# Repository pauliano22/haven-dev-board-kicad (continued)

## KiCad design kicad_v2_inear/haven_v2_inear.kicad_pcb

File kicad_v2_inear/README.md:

# Haven v2 BTE in-ear unit: schematic

The small board in the in-ear unit: SPH0641 PDM mic (the primary mic; SELECT low = DMIC0) (bottom port, needs a hole through the
board), 100 nF decoupling, a 33 Ω series resistor on the mic's data line, six cable pads and two
speaker pads. Target outline about 6 × 6 mm, 2-layer, 0.6 mm.

The design notes, cable harness table and decisions are in `../kicad_v2_pod/README.md`. Both
schematics are generated by `tools/gen_v2_bte_schematic.py`.

For the 2-wire variant (pod mic only), leave the mic, C1 and R1 off, or skip this board and wire the speaker straight to cable W5/W6.

## Layout (`haven_v2_inear.kicad_pcb`)

Generated by `tools/gen_v2_inear_pcb.py`. The script places, routes, pours and fills, and writes the
design rules into the `.kicad_pro`. Results: DRC 0 violations, 0 unconnected, and schematic parity 0
(`kicad-cli pcb drc --schematic-parity --severity-all`).

- 6 × 6 mm, 2-layer, 0.6 mm, corner radius 0.8. The outline matches haven-hardware
  `mechanical_cad/v2_bte/board_inear_outline.dxf`. One board fits both ears.
- **Bottom (driver side):** U13 SPH0641LU4H-1. It is bottom-port (datasheet / DigiKey "Port
  Location: Bottom"), so its port sits on a plated 0.4 mm hole at the board centre. That hole is
  pad 3 (GND), added to the footprint and lined up with the shell's mic hole. The driver pads
  TP1/TP2 sit on the same face as the speaker.
- **Top (lateral side):** cable pads W1..W6, with C1 next to W1 and R1 in the DATA line. Nothing
  is placed within 1.4 mm of the port (`GASKET_KEEPOUT` rule area), so a 0.5 mm foam gasket can
  seal the board to the shell's mic hole.
- Rules (JLCPCB 2-layer standard): 0.15 mm tracks, 0.127 mm clearance, 0.3 / 0.55 mm vias,
  0.25 mm copper to edge. GND is poured on both layers.

Before ordering, check:
- The port hole and the paste on the four GND pads around it, against the Knowles land-pattern
  drawing. Solder must not flow into the port. If it might, trim the paste on the inner corners.
- The SPK and cable wire pads (0.8 mm) are for hand soldering 6-wire harness conductors under
  a microscope. Vias are in the pads, which is fine for hand soldering.

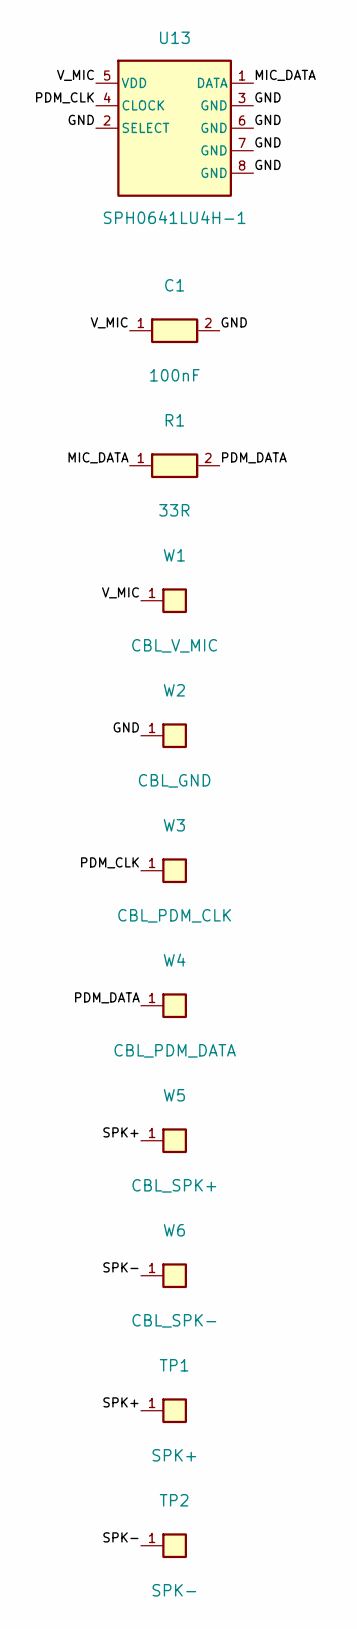
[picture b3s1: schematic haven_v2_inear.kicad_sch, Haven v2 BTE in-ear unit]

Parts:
C1: 100nF; C0201; MPN GRM033R60J104KE19D; LCSC C76928
R1: 33R; R0201; MPN ERJ1GNF33R0C; LCSC C717007
TP1: SPK+; Pad_1.2
TP2: SPK-; Pad_1.2
U13: SPH0641LU4H-1; MIC-SMD_5P_L3.5-W2.7-P0.82_SPH0641LU4H-1; MPN SPH0641LU4H-1; LCSC C2879853
W1: CBL_V_MIC; WirePad_0.8
W2: CBL_GND; WirePad_0.8
W3: CBL_PDM_CLK; WirePad_0.8
W4: CBL_PDM_DATA; WirePad_0.8
W5: CBL_SPK+; WirePad_0.8
W6: CBL_SPK-; WirePad_0.8

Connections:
/GND: C1.2, U13.2 (SELECT), U13.3 (GND), U13.6 (GND), U13.7 (GND), U13.8 (GND), W2.1
/MIC_DATA: R1.1, U13.1 (DATA)
/PDM_CLK: U13.4 (CLOCK), W3.1
/PDM_DATA: R1.2, W4.1
/SPK+: TP1.1, W5.1
/SPK-: TP2.1, W6.1
/V_MIC: C1.1, U13.5 (VDD), W1.1

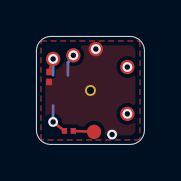
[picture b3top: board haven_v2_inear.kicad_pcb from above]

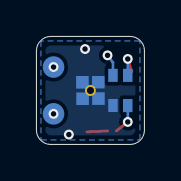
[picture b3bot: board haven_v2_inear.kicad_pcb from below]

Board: 2 copper layers, 6.0 x 6.0 mm, 11 parts (3 on the bottom side), 7 nets.

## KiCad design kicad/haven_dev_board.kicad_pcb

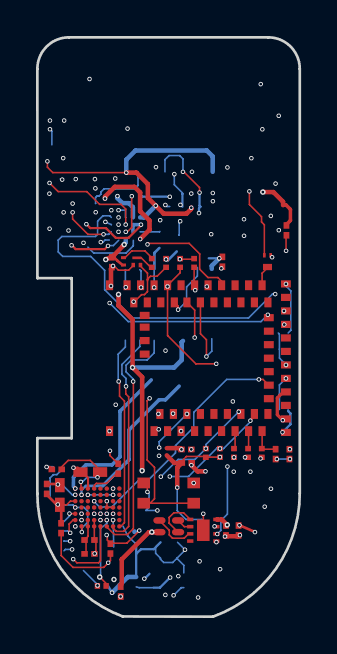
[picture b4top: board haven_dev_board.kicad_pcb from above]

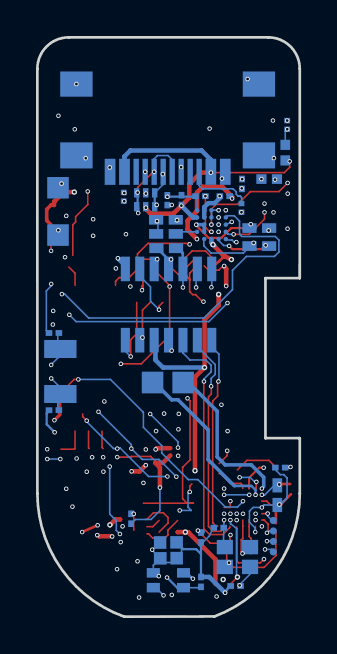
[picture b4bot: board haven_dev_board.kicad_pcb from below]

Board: 6 copper layers, 14.6 x 32.2 mm, 77 parts (39 on the bottom side), 61 nets.

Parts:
C1, C5, C7, C9, C10, C21, C29, C32, C36, C47: 1uF.1; C0201
C2, C14: 9pF.1; C0201
C3, C4: 4.7uF.1; C0201
C11, C12, C13, C27, C31, C38, C40, C42, C43, C44, C48: 100nF.1; C0201
C16, C20: 4.7uF, 10V.1; C0402
C17, C19, C22: 1uF >10V.1; C0201
C18: 10uF, >4V.1; C0402
C33, C34, C41: 10uF.1; C0402
C45, C46: GRM0335C1H330JA01D.1; b5c2858cad4e462ab76a8d0ccf4ade45
C49: C0402C103J3RACAUTO.1; cef4f92115b54348803d28f8706b0456
CRYSTAL1: CN4024M57620001.1; 6684822644394e4eba542a27714dd8a6
D2: PRTR5V0U2F.1; SON-6_L1.5-W1.0-P0.50-BL
J1: CLE-107-01-G-DV.1; CLE-107-01-X-DV
L2: 2.2uH.1; L0402
LED3: MHPA1010RGBDT.1; LED-ARRAY-SMD_4P-L1.0-W1.0-TR-RD
MDBT531: MDBT53.1; MDBT53
Q1: CSD23382F4.1; PICOSTAR-3_L1.0-W0.6-P0.35-TL
Q2: CSD13380F3T.1; PICOSTAR-3_L0.7-W0.6-P0.40-TL
R2, R3: 10kΩ.1; R0201
R4: 510Ω.1; R0201
R5, R9: 2kΩ.1; R0201
R6: 51kΩ.1; R0201
R7, R8: 5.1kΩ.1; R0201
R13: 37.4kΩ, 1%.1; R0402
R21: 0R; R0402
R23, R26: 27Ω.1; R0201
R27: 2.2Ω.1; R0201
R28: RC0201FR-07220RL.1; ea94e26560f84db4a6862024f5c3efa7
SW1: TS2819A 230GF.1; SW-SMD_4P-L2.8-W1.9-P1.16-LS3.0
TP_BAT+: pad; free_pad
TP_BAT-: pad; free_pad
TP_BCLK: pad; free_pad
TP_DIN: pad; free_pad
TP_DOUT: pad; free_pad
TP_LRCLK: pad; free_pad
TP_SPK+: pad; free_pad
TP_SPK-: pad; free_pad
U2: BQ25120AYFPR.1; DSBGA-25_L2.5-W2.6-R5-C5-P0.40-BL
U3: AP22916BCA4-7.1; X1-WLB0808-4_L0.8-W0.8-P0.40-TL
U4: XL-0201SURC.1; LED-SMD_L0.65-W0.35-P0.41_XL-0201SURC
U5: KTD2026.1; DFN-8_L1.5-W1.5-P0.40-BL-EP
U8: 1MΩ.1; R0201
U12: GT-USB-9047A.1; USB-C-SMD_GT-USB-9047A
U13: SPH0641LU4H-1.1; MIC-SMD_5P_L3.5-W2.7-P0.82_SPH0641LU4H-1
U15: ADAU1860BCBZRL.1; BGA-56_L3.0-W2.7-P0.35-R8-C7-TL
X1: Q13FC1350000200.1; FC-135R_L3.2-W1.5

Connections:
3V3: C5.2, C17.1, C29.2, C48.1, J1.10, LED3.1, U2.C5, U4.1, U5.5
#ERROR: MDBT531.3, Q2.1, U8.1
$1N48: R7.2, U12.A5
$1N49: R8.2, U12.B5
$1N65: C10.1, U2.C4
$1N98: C3.1, MDBT531.44, R27.2
$1N117: Q2.3, R4.2
$1N119: R4.1, U4.2
$1N151: C31.1, C36.1, U15.A3, U15.B3
$1N2586: C32.1, U15.G4
$1N16368: C45.1, CRYSTAL1.3, R28.1
+1.8V: C1.2, C4.2, C18.1, C20.2, J1.9, L2.2, MDBT531.38, MDBT531.41, Q1.2, R2.1, R3.1, U2.B5, U3.A2
BCLK: MDBT531.59, TP_BCLK.1, U15.B2
CC_#CD: MDBT531.26, U2.E2
CC_#PG: MDBT531.16, U2.D4
DAC_ENABLE: MDBT531.37, U15.E4
DAC_N: TP_SPK-.1, U15.G1
DAC_P: TP_SPK+.1, U15.F2
DIN: MDBT531.60, TP_DIN.1, U15.C1
DOUT: MDBT531.56, TP_DOUT.1, U15.B1
GND: C1.1, C2.1, C3.2, C4.1, C5.1, C7.2, C9.2, C10.2, C11.1, C12.1, C13.2, C14.1, C16.1, C17.2, C18.2, C19.2, C20.1, C21.1, C22.2, C27.1, C29.1, C31.2, C32.2, C33.1, C34.2, C36.2, C38.1, C40.2, C41.2, C42.1, C43.2, C44.2, C45.2, C46.1, C47.2, C48.2, C49.1, CRYSTAL1.2, CRYSTAL1.4, D2.2, J1.7, MDBT531.1, MDBT531.24, MDBT531.42, MDBT531.61, Q2.2, R6.1, R7.1, R8.1, SW1.3, SW1.4, TP_BAT-.1, U2.A1, U2.A5, U2.C1, U2.C2, U2.D1, U2.D5, U3.B1, U5.8, U5.9, U8.2, U12.12, U12.13, U12.14, U12.15, U12.A1B12, U12.A12B1, U13.2, U13.3, U13.6, U13.7, U13.8, U15.A1, U15.A4, U15.B4, U15.D6, U15.D7, U15.E6, U15.F1, U15.G3, U15.G7
INT: MDBT531.14, U2.D2
IO1: J1.11, MDBT531.9
IO2: J1.12, MDBT531.11
IO3: J1.14, MDBT531.13
LRCLK: MDBT531.57, TP_LRCLK.1, U15.C2
LSCTRL: MDBT531.27, U2.E3
MR#: Q1.1, SW1.1, SW1.2, U2.E1
ON+BTN: MDBT531.22, Q1.3
PDMCLK: U13.4, U15.C4
PDMDIN: U13.1, U15.C5
RESETN: C49.2, J1.5, MDBT531.6, U2.D3
RGB_B: LED3.4, U5.2
RGB_G: LED3.3, U5.3
RGB_R: LED3.2, U5.4
SCL: MDBT531.8, R3.2, U2.E5, U5.6
SCL1: MDBT531.45, R9.2, U15.C7
SDA: MDBT531.12, R2.2, U2.E4, U5.7
SDA1: MDBT531.47, R5.2, U15.C6
SENSORS_ENABLE: MDBT531.55, U3.B2
SW: L2.1, U2.A4
SWCLK: J1.1, MDBT531.2
SWDIO: J1.3, MDBT531.4
TCK: J1.8, U15.A5
TDI: J1.2, U15.A8
TDO: J1.4, U15.A7
TMS: J1.6, U15.A6
TS: R6.2, R13.1, U2.C3
USB_D+: MDBT531.46, R23.2
USB_D-: MDBT531.48, R26.2
USB_DM: D2.1, D2.6, R26.1, U12.A7, U12.B7
USB_DP: D2.3, D2.4, R23.1, U12.A6, U12.B6
VCC: C19.1, R21.2, U2.B1, U2.B2
VUSB: C22.1, D2.5, R13.2, R27.1, U2.A2, U12.A4B9, U12.A9B4
V_BAT: C21.2, R21.1, TP_BAT+.1
V_LS: C7.1, C11.2, C12.2, C13.1, C27.2, C33.2, C34.1, C38.2, C40.1, C41.1, C42.2, C43.1, C44.1, C47.1, J1.13, R5.1, R9.1, U3.A1, U13.5, U15.A2, U15.B5, U15.D1, U15.E1, U15.F3, U15.F7, U15.G2
V_PMID: C9.1, C16.2, U2.A3, U2.B3, U2.B4
XL1: C14.2, MDBT531.34, X1.1
XL2: C2.2, MDBT531.36, X1.2
XTALI: C46.2, CRYSTAL1.1, U15.B7
XTALO: R28.2, U15.B6

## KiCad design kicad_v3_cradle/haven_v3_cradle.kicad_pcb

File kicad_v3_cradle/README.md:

# Haven v3 charging cradle (2026-11-14)

A desk cradle that charges both v3 pods from any USB-C charger. No battery, no charging chip: each pod has its own
(nPM1100). The cradle only brings 5 V to the pods' two spring pins.

**Why a cradle and not a charging case:** a case carries its own battery and charger board and is a project of its
own. The first pair only needs to charge; this does that with four cheap parts. A case can come later.

## Parts

| Part | Made by | Source |
|---|---|---|
| Dock board, 41 x 51.5 mm, 2 layers, 1.6 mm, ENIG (the pads must be gold) | JLCPCB, fully assembled, nothing to solder | `tools/gen_cradle_v3_pcb.py` -> `haven_v3_cradle.kicad_pcb`, fab files in `fab/v3_cradle/` |
| Base, frame, lid (printed, about 9 g each) | any resin or FDM print service | `hardware/mechanical_cad/v3_slim/cradle_v3.py` -> `cradle_v3_{base,frame,lid}.stl` |
| 8 disc magnets 5 x 2 mm N52, 4 screws M2 x 8 self-tapping | bought | glued into the frame top and lid underside; screws go through frame and board into the base |

Board parts (LCSC numbers from memory, **check them at the JLCPCB quote**): J1 USB-C TYPE-C-31-M-12 (C165948),
R1 / R2 5.1 kohm 0603 (C23186, tell the charger to give 5 V), C1 10 uF 0603 (C19702). Four bare pads CP1-CP4.

## How a pod sits

- Head-side face down in a pocket shaped like the pod. Its two spring pins (pod board P1 = VBUS, P2 = GND) land on two
  1.8 mm gold pads on a tongue of the board; "+" and "-" are printed beside them.
- The pod shell now has a **flat contact land** around the pins (z = -4.4, 5.4 x 4.0 mm, wall thickened inside to
  0.8 mm; `LAND_*` in `pod_v3_styled.py`). Before this the face sloped about 25 degrees there and a flat pad would
  have hit the shell first. With the 4.5 mm pin the tip stands 0.5 mm proud of the land and the pad pushes it in 0.5 mm
  (half its 1.0 mm working travel).
- The rest of the pod's curved head side goes through a hole in the board into a printed cup with 0.3 mm clearance, so
  the pod rests on the land, not the cup.
- The lid rests on the pods (0.3 mm above the frame) and four magnet pairs pull it down, so the magnets' pull presses
  the pods onto the pads. Spring-pin force: 130 gf +-20 % each at the 1.0 mm working point (datasheet); at 0.5 mm it
  is less, not given.
- The speaker cable leaves through an open slot at each pocket's cable end; the lid has a groove over it.
- Both pods are the same part (the v3 pod is mirror-symmetric across its width, so the same pod rotated serves the
  other ear), so both pockets are the same.

## Checks run

- Board: KiCad DRC 0 errors, 0 unconnected, 2 silkscreen warnings. Board outline, holes, tongues, pads and screws are
  read from `cradle_v3_layout.json`, written by the cradle script, so the two cannot drift apart.
- Cradle script asserts: the pod never dips into the board outside the holes; every pad is on board; base, frame and
  lid do not overlap; the lid reaches the pods. Section picture: `cradle_v3_section.png`.

Review (2026-11-14, after the first build):
- Polarity traced from the pod board file to the dock board file: on both pods P1 (VBUS) lands on a VBUS pad and P2
  (GND) on a GND pad. A pod put in turned around lands its pins on the printed cup: no contact, so it cannot be
  reverse-powered. Upside down, the pins face up: no contact.
- The real shell meshes placed in the cradle: no overlap with the base or frame (closest 0.05 mm to the cups, 0.15 mm
  to the pocket walls); the lid presses 0.06 mm into the pod lids, which is the intended contact.
- Added after review: a thumb notch in the frame at the cable end, so the magnet lid can be lifted.
- Screws: M2 x 8 goes through 4.2 mm of frame and the 1.6 mm board and 2.2 mm into the 3 mm base; it does not come
  out the bottom.

## Not checked / open

- Nothing printed or built. Magnet strength in practice; real contact force at 0.5 mm; print tolerances.
- No fuse and no ESD part: a coin across a + and - pad shorts the charger's 5 V (USB chargers current-limit; cheap ones
  may not). The pads are under the pods, recessed in the pockets.
- No parking spot for the in-ear pieces; they hang out on their cables.
- Only the A4/B9 VBUS pins of the socket are wired (all four VBUS contacts are one wire inside a USB-C plug).

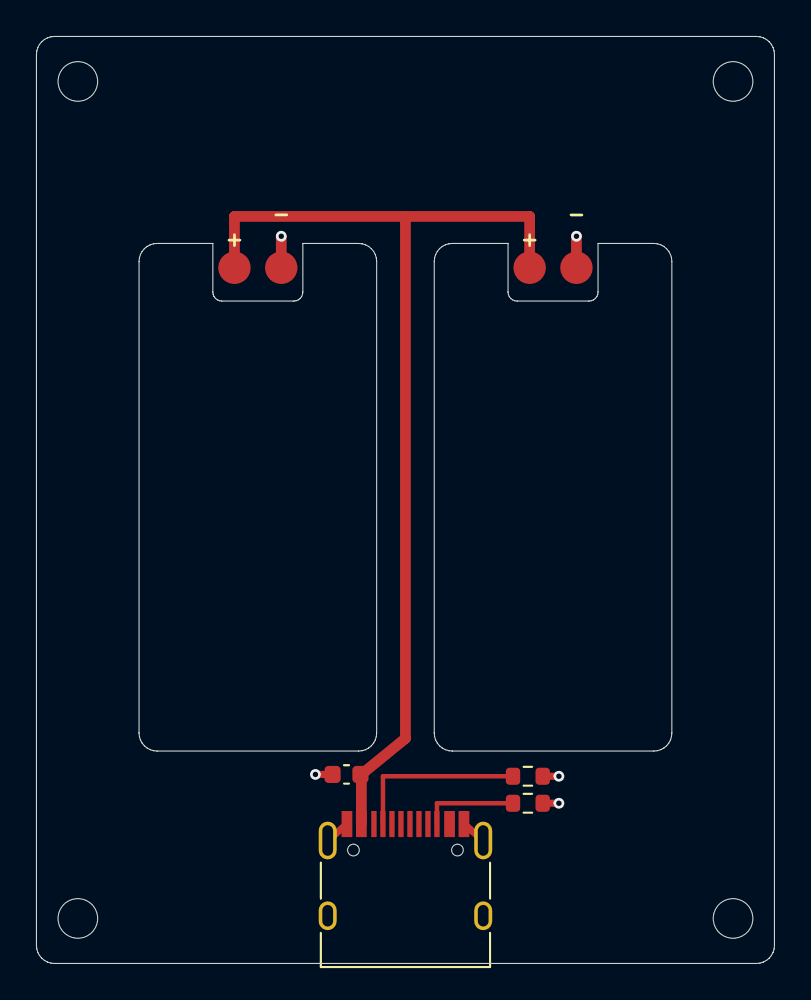
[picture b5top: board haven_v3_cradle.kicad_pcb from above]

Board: 2 copper layers, 41.0 x 51.5 mm, 12 parts (0 on the bottom side), 5 nets.

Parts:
C1: 10uF 10V; C_0603_1608Metric
CP1, CP3: VBUS
CP2, CP4: GND
H1, H2, H3, H4: M2; MountingHole_2.2mm_M2
J1: USB-C power; USB_C_Receptacle_HRO_TYPE-C-31-M-12
R1, R2: 5.1k; R_0603_1608Metric

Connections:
CC1: J1.A5, R1.1
CC2: J1.B5, R2.1
GND: C1.1, CP2.1, CP4.1, J1.A1, J1.A12, J1.B1, J1.B12, J1.S1, R1.2, R2.2
VBUS: C1.2, CP1.1, CP3.1, J1.A4, J1.B9
VBUS_B: J1.A9, J1.B4

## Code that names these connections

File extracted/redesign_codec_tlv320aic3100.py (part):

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    established (TPS62822's regulated output) -- reused for the codec's
    DVDD, which needs 1.65-1.95V per its own datasheet. This only works
    because that redesign landed first.
  - DAC_N/DAC_P: ADAU1860's HPOUTN/HPOUTP were labeled with these but had
    only ONE owner each on this sheet (the chip itself) -- the real
    downstream receiver connection isn't modeled here, a pre-existing
    condition, not something this change creates or fixes. Preserved
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    whatever else might be on that chain.

Real, deliberate simplifications (each flagged, not hidden):
  - MCLK (pin 8) is tied to the same net as BCLK (pin 7) rather than
    adding a dedicated crystal -- TLV320AIC3100's own datasheet explicitly
    says "normally MCLK is PLL input; however, BCLK, GPIO1, etc. can also
    be PLL input," so the PLL is configured (in firmware/register init,
    not modeled here) to use BCLK as its reference instead. Avoids needing
    a new crystal for a part that didn't need its own oscillator before.
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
